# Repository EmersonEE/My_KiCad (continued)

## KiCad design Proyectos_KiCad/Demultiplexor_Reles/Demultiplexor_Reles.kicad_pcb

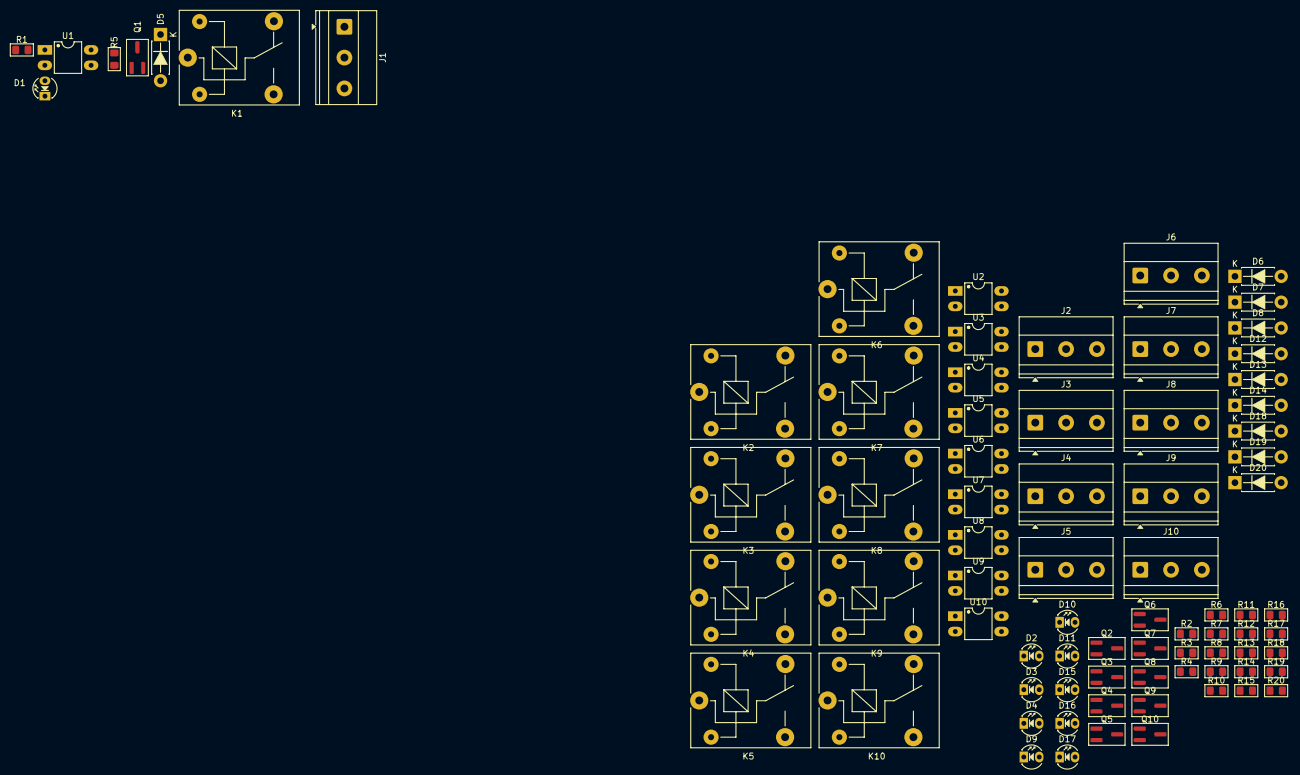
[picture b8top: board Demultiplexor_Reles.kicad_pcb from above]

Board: 2 copper layers, 80 parts (0 on the bottom side), 82 nets, no tracks yet.

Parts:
D1, D2, D3, D4, D9, D10, D11, D15, D16, D17: LED_OPTO; LED_D3.0mm
D5, D6, D7, D8, D12, D13, D14, D18, D19, D20: 1N4007; D_DO-41_SOD81_P7.62mm_Horizontal
J1, J2, J3, J4, J5, J6, J7, J8, J9, J10: RELE; TerminalBlock_Phoenix_MKDS-1,5-3-5.08_1x03_P5.08mm_Horizont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
K1, K2, K3, K4, K5, K6, K7, K8, K9, K10: SANYOU_SRD_Form_C; Relay_SPDT_SANYOU_SRD_Series_Form_C
Q1, Q2, Q3, Q4, Q5, Q6, Q7, Q8, Q9, Q10: 2N3904; SOT-23W_BigPads
R1, R2, R3, R4, R9, R10, R11, R15, R16, R17: 200; R_0805_2012Metric_Pad1.15x1.40mm
R5, R6, R7, R8, R12, R13, R14, R18, R19, R20: 1K; R_0805_2012Metric_Pad1.15x1.40mm
U1, U2, U3, U4, U5, U6, U7, U8, U9, U10: PC817; DIP-4_W7.62mm_LongPads

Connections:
+5V: D5.1 (K), D6.1 (K), D7.1 (K), D8.1 (K), D12.1 (K), D13.1 (K), D14.1 (K), D18.1 (K), D19.1 (K), D20.1 (K), K1.5, K2.5, K3.5, K4.5, K5.5, K6.5, K7.5, K8.5, K9.5, K10.5, U1.4, U2.4, U3.4, U4.4, U5.4, U6.4, U7.4, U8.4, U9.4, U10.4
COM: J1.2, K1.1
COM_2: J2.2, K2.1
COM_3: J3.2, K3.1
COM_4: J5.2, K5.1
COM_5: J6.2, K6.1
COM_6: J7.2, K7.1
COM_7: J8.2, K8.1
COM_8: J9.2, K9.1
COM_9: J10.2, K10.1
COM_10: J4.2, K4.1
GND: D1.1 (K), D2.1 (K), D3.1 (K), D4.1 (K), D9.1 (K), D10.1 (K), D11.1 (K), D15.1 (K), D16.1 (K), D17.1 (K), Q1.1 (E), Q2.1 (E), Q3.1 (E), Q4.1 (E), Q5.1 (E), Q6.1 (E), Q7.1 (E), Q8.1 (E), Q9.1 (E), Q10.1 (E)
NA: J1.3, K1.3
NA_2: J2.3, K2.3
NA_3: J3.3, K3.3
NA_4: J5.3, K5.3
NA_5: J6.3, K6.3
NA_6: J7.3, K7.3
NA_7: J8.3, K8.3
NA_8: J9.3, K9.3
NA_9: J10.3, K10.3
NA_10: J4.3, K4.3
NC: J1.1, K1.4
NC_2: J2.1, K2.4
NC_3: J3.1, K3.4
NC_4: J5.1, K5.4
NC_5: J6.1, K6.4
NC_6: J7.1, K7.4
NC_7: J8.1, K8.4
NC_8: J9.1, K9.4
NC_9: J10.1, K10.4
NC_10: J4.1, K4.4
unnamed: D1.2 (A), U1.2
unnamed: D2.2 (A), U2.2
unnamed: D3.2 (A), U3.2
unnamed: D4.2 (A), U4.2
unnamed: D5.2 (A), K1.2, Q1.3 (C)
unnamed: D6.2 (A), K2.2, Q2.3 (C)
unnamed: D7.2 (A), K3.2, Q3.3 (C)
unnamed: D8.2 (A), K4.2, Q4.3 (C)
unnamed: D9.2 (A), U5.2
unnamed: D10.2 (A), U6.2
unnamed: D11.2 (A), U7.2
unnamed: D12.2 (A), K5.2, Q5.3 (C)
unnamed: D13.2 (A), K6.2, Q6.3 (C)
unnamed: D14.2 (A), K7.2, Q7.3 (C)
unnamed: D15.2 (A), U8.2
unnamed: D16.2 (A), U9.2
unnamed: D17.2 (A), U10.2
unnamed: D18.2 (A), K8.2, Q8.3 (C)
unnamed: D19.2 (A), K9.2, Q9.3 (C)
unnamed: D20.2 (A), K10.2, Q10.3 (C)
unnamed: Q1.2 (B), R5.2
unnamed: Q2.2 (B), R6.2
unnamed: Q3.2 (B), R7.2
unnamed: Q4.2 (B), R8.2
unnamed: Q5.2 (B), R12.2
unnamed: Q6.2 (B), R13.2
unnamed: Q7.2 (B), R14.2
unnamed: Q8.2 (B), R18.2
unnamed: Q9.2 (B), R19.2
unnamed: Q10.2 (B), R20.2
unnamed: R1.2, U1.1
unnamed: R2.2, U2.1
unnamed: R3.2, U3.1
unnamed: R4.2, U4.1
unnamed: R5.1, U1.3
unnamed: R6.1, U2.3
unnamed: R7.1, U3.3
unnamed: R8.1, U4.3
unnamed: R9.2, U5.1
unnamed: R10.2, U6.1
unnamed: R11.2, U7.1
unnamed: R12.1, U5.3
unnamed: R13.1, U6.3
unnamed: R14.1, U7.3
unnamed: R15.2, U8.1
unnamed: R16.2, U9.1
unnamed: R17.2, U10.1
unnamed: R18.1, U8.3
unnamed: R19.1, U9.3
unnamed: R20.1, U10.3

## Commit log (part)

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2025-04-19 Proyectos CachyOS
2025-05-17 Librerias
2025-05-29 NuevoSimbolo
2025-06-08 Por si cambio
2025-06-09 Agregando Resistencias
2025-06-14 Asistencia
2025-06-29 Agregando Disign Block
2025-06-29 Separando Proyectos
2025-06-30 Leds Colores
2025-07-05 Librerias y Esquematico
2025-07-06 Router
2025-07-06 Arreglando Leds
2025-07-14 Caja Terminada
2025-07-22 Todo por si cambio
2025-07-29 Placa entrenadora esp32-38
2025-08-04 Añadiendo Bloques SMD
2025-08-16 Articulaciones
2025-09-08 Punta Logica
2025-09-08 WS2812 NANO
2025-09-21 Por si cambio xd
2025-10-01 Agregando Modelos 3D
2025-10-01 AGregando Drivers
2025-10-01 Creando Huellas
2025-10-01 Placa Para el Brazo
2025-10-01 Placa Eddy
2025-10-03 Librerias Modificadas
2025-10-03 Placa Eddy Terminada
2025-10-03 Placa Brazo
2025-10-06 Añadiendo Lagrimas
2025-10-11 Por si cambio a gnome
2025-10-14 Agregando modulos INA219 - ACS712
2025-10-14 Routeo Termiando
2025-10-18 Cambiando a Omarchy
2025-10-21 Empezando Sumador-Restador
2025-11-15 Por si valgo
2025-11-28 Nuevos Esquematicos
2025-11-28 Placa 555 Astable
2025-11-28 555 PWM
2025-11-28 Placa Para sensor TPS
2025-11-28 Cambios Fuente
2025-11-30 Moviendo el RTC y el WEMOS
2025-12-08 Arreglando RAM
2026-01-24 Placa Entrenadora V2
2026-01-24 Bloques
2026-01-24 Hola
2026-03-03 Nuevos Proyectos
2026-03-20 Por si las dudas
2026-04-15 Shiel-ULN2803-BPM
2026-05-09 Omarchy-RIP
